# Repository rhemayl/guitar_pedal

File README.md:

# GuitarPedal

## Author

<!-- Insert Your Name Here -->

## Description

<!-- Describe your example here -->

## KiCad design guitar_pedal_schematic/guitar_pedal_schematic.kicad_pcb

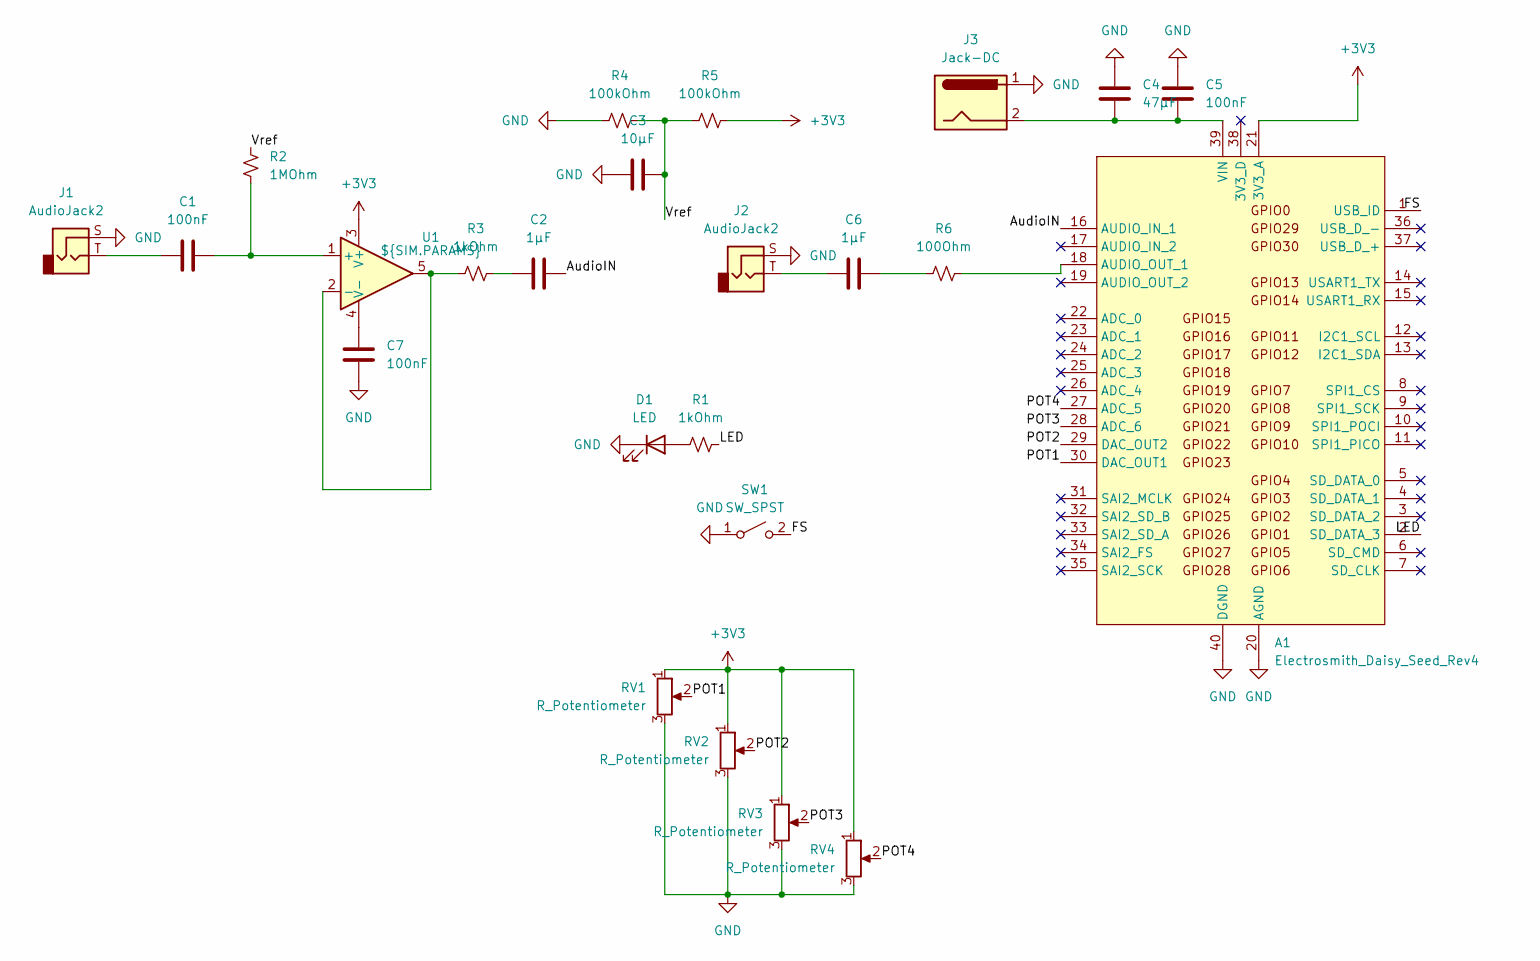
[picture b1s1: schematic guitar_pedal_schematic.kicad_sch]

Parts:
A1: Electrosmith_Daisy_Seed_Rev4; Electrosmith_Daisy_Seed
C1, C5, C7: 100nF; C_0805_2012Metric_Pad1.18x1.45mm_HandSolder
C2, C6: 1µF; C_0805_2012Metric_Pad1.18x1.45mm_HandSolder
C3: 10µF; C_0805_2012Metric_Pad1.18x1.45mm_HandSolder
C4: 47µF; CP_Elec_6.3x7.7
D1: LED; SolderWire-0.5sqmm_1x02_P4.6mm_D0.9mm_OD2.1mm
J1, J2: AudioJack2; SolderWire-0.5sqmm_1x02_P4.6mm_D0.9mm_OD2.1mm
J3: Jack-DC; SolderWire-0.5sqmm_1x02_P4.6mm_D0.9mm_OD2.1mm
R1, R3: 1kOhm; R_Axial_DIN0207_L6.3mm_D2.5mm_P10.16mm_Horizontal
R2: 1MOhm; R_Axial_DIN0207_L6.3mm_D2.5mm_P10.16mm_Horizontal
R4, R5: 100kOhm; R_Axial_DIN0207_L6.3mm_D2.5mm_P10.16mm_Horizontal
R6: 100Ohm; R_Axial_DIN0207_L6.3mm_D2.5mm_P10.16mm_Horizontal
RV1, RV2, RV3, RV4: R_Potentiometer; SolderWire-0.5sqmm_1x03_P4.6mm_D0.9mm_OD2.1mm
SW1: SW_SPST; SolderWire-0.5sqmm_1x02_P4.6mm_D0.9mm_OD2.1mm
U1: ${SIM.PARAMS}; SOT-23-5_HandSoldering

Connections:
+3V3: A1.21 (3V3_A), R5.2, RV1.1, RV2.1, RV3.1, RV4.1, U1.3 (V+)
/AudioIN: A1.16 (AUDIO_IN_1), C2.2
/FS: A1.1 (USB_ID), SW1.2 (B)
/LED: A1.2 (SD_DATA_3), R1.2
/POT1: A1.30 (DAC_OUT1), RV1.2
/POT2: A1.29 (DAC_OUT2), RV2.2
/POT3: A1.28 (ADC_6), RV3.2
/POT4: A1.27 (ADC_5), RV4.2
/Vref: C3.2, R2.1, R4.2, R5.1
GND: A1.20 (AGND), A1.40 (DGND), C3.1, C4.2, C5.1, C7.2, D1.1 (K), J1.S, J2.S, J3.1, R4.1, RV1.3, RV2.3, RV3.3, RV4.3, SW1.1 (A)
unnamed: A1.18 (AUDIO_OUT_1), R6.2
unnamed: A1.39 (VIN), C4.1, C5.2, J3.2
unnamed: C1.1, J1.T
unnamed: C2.1, R3.2
unnamed: C6.1, J2.T
unnamed: C6.2, R6.1
unnamed: D1.2 (A), R1.1
unnamed: C1.2, R2.2, U1.1 (+)
unnamed: R3.1, U1.2 (-), U1.5
unnamed: C7.1, U1.4 (V-)

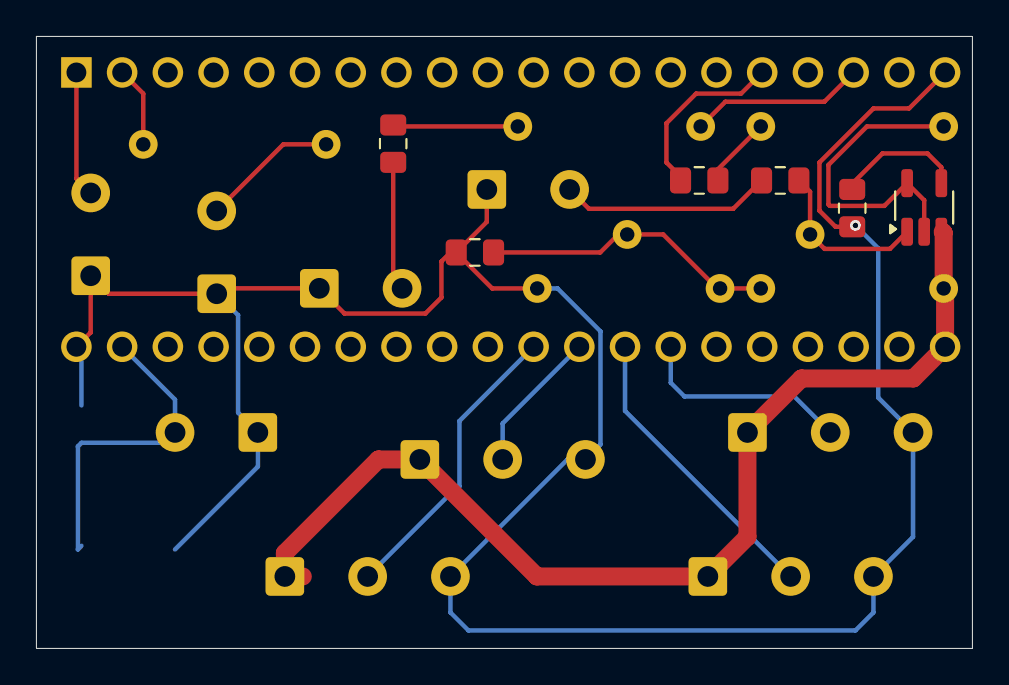
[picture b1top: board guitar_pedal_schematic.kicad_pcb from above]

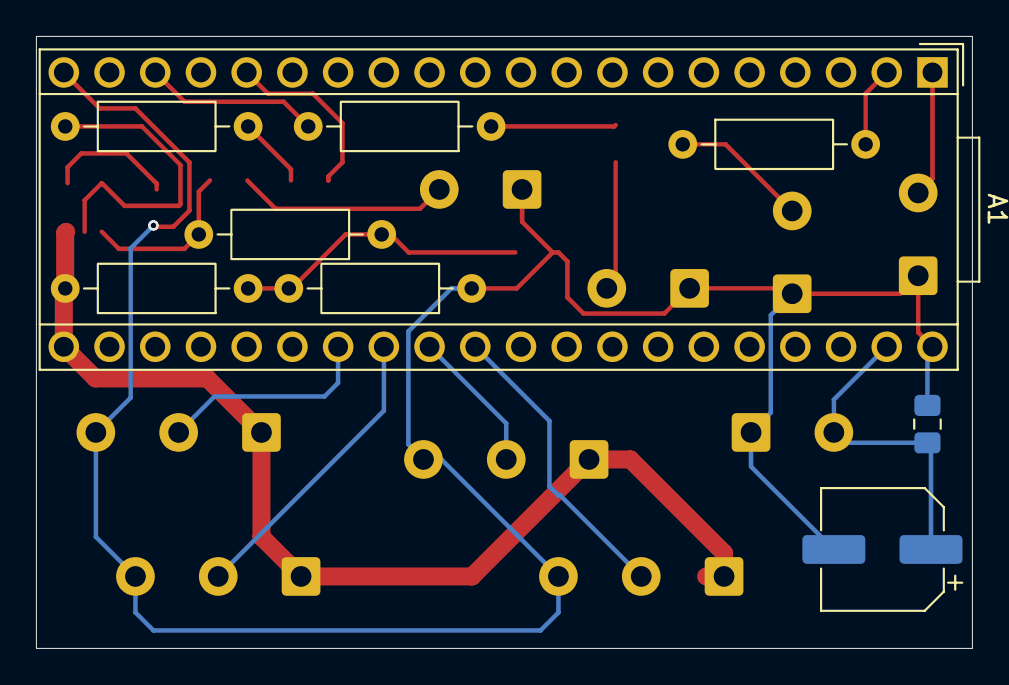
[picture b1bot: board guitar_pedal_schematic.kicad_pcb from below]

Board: 2 copper layers, 52.0 x 34.0 mm, 24 parts (13 on the bottom side), 20 nets.

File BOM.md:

| Part | Quantity |
| ------------- | ------------- |
| PCB  | 1  |
| Pedal Enclousure | 1  |
| Electrosmith Daisy Seed  | 1  |
| Audio Jack 6.35mm | 2  |
| DC Jack DC-022B 5.5*2.1mm  | 1  |
| 47uF Capacitor Electrolytic 6.3*7.7mm  | 1  |
| 10uF Capacitor 0805 X7R  | 1  |
| 1uF Capacitor 0805 X7R  | 2  |
| 100nF Capacitor 0805 X7R  | 3  |
| 1MOhm Resistor  | 1  |
| 100kOhm Resistor  | 2  |
| 1kOhm Resistor  | 2  |
| 100Ohm Resistor  | 1  |
| 3 Pin Potentiometer Type B 10K WH148  | 4  |
| Potentiometer Cap  | 4  |
| Switch R13-85A  | 1  |
| Op-amp MCP6001T-I  | 1  |
| LED | 1  |

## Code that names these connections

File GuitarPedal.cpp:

#include "daisy_seed.h"
#include "daisysp.h"
  
using namespace daisy;
using namespace daisysp;

DaisySeed hw;

Phaser phaser;
bool effect_state;
float pot0 = 1;
float pot1 = 1;
float pot2 = 1;
float pot3 = 1;



void AudioCallback(AudioHandle::InputBuffer in, AudioHandle::OutputBuffer out, size_t size)
{
	float processedSignal;
	pot0 = hw.adc.GetFloat(0);
	pot1 = hw.adc.GetFloat(1);
	pot2 = hw.adc.GetFloat(2);
	pot3 = hw.adc.GetFloat(3);
	float distortionAmount = pot0 *50 +1;
	float rate = 0.1 * powf(50, pot1);
	float depth = pot2;
	float feedback = pot3 * 0.9;

	phaser.SetLfoFreq(rate);
	phaser.SetLfoDepth(depth);
    phaser.SetFeedback(feedback);

	for (size_t i = 0; i < size; i++)
	{	
		if (effect_state) {
			processedSignal = phaser.Process(in[0][i]);
			processedSignal = processedSignal * distortionAmount;

			if (processedSignal > 1) {
				processedSignal = 2.0f/3.0f;
			} else if (processedSignal < -1) {
				processedSignal = -2.0f/3.0f;
			} else {
				processedSignal = processedSignal - (processedSignal*processedSignal*processedSignal)/3;
			}
			out[0][i]=processedSignal;
		} else {
			out[0][i]=in[0][i];
		}

	}
}

int main(void)
{
	hw.Init();

	phaser.Init(48000);
	phaser.SetPoles(6);
    phaser.SetFreq(500.0);


	GPIO LED;
	LED.Init(seed::D1, GPIO::Mode::OUTPUT);

	Switch effect_switch;
	effect_switch.Init(seed::D0);


	AdcChannelConfig pots[4];
	pots[0].InitSingle(seed::A5);
	pots[1].InitSingle(seed::A6);
	pots[2].InitSingle(seed::A7);
	pots[3].InitSingle(seed::A8);
	hw.adc.Init(pots, 4);
	hw.adc.Start();

	hw.SetAudioBlockSize(4); // number of samples handled per callback
	hw.SetAudioSampleRate(SaiHandle::Config::SampleRate::SAI_48KHZ);
	hw.StartAudio(AudioCallback);

	while(1) {
		effect_switch.Debounce();
		if (effect_switch.RisingEdge()) {
			effect_state = !effect_state;
			LED.Write(effect_state);
		}
	}
}
